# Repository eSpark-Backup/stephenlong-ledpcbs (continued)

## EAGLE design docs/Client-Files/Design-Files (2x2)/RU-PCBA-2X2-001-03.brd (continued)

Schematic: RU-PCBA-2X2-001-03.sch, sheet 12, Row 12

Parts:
C267, C268, C269, C270, C271, C272, C273, C274, C275, C276, C277, C278, C279, C280, C281, C282, C283, C284, C285, C286, C287, C288, C289, C290: C-EUC1206; C1206; MPN C_104
LD799, LD805, LD811, LD817, LD823, LD829, LD835, LD841, LD847, LD853, LD859, LD865: R; 5050LED; MPN R_5050
LD800, LD806, LD812, LD818, LD824, LD830, LD836, LD842, LD848, LD854, LD860, LD866: G; 5050LED; MPN G_5050
LD801, LD807, LD813, LD819, LD825, LD831, LD837, LD843, LD849, LD855, LD861, LD867: B; 5050LED; MPN B_5050
LD802, LD808, LD814, LD820, LD826, LD832, LD838, LD844, LD850, LD856, LD862, LD868: A; 5050LED; MPN A_5050
LD803, LD809, LD815, LD821, LD827, LD833, LD839, LD845, LD851, LD857, LD863, LD869: C; 5050LED; MPN C_5050
LD804, LD810, LD816, LD822, LD828, LD834, LD840, LD846, LD852, LD858, LD864, LD870: L; 5050LED; MPN L_5050
R1331, R1336, R1341, R1346, R1351, R1356, R1361, R1366, R1371, R1376, R1381, R1386, R1391, R1396, R1401, R1406, R1411, R1416, R1421, R1426, R1431, R1436, R1441, R1446: 2k; R1206; MPN R_VDD
R1332, R1333, R1337, R1338, R1342, R1343, R1347, R1348, R1352, R1353, R1357, R1358, R1362, R1363, R1367, R1368, R1372, R1373, R1377, R1378, R1382, R1383, R1387, R1388, R1392, R1393, R1397, R1398, R1402, R1403, R1407, R1408, R1412, R1413, R1417, R1418, R1422, R1423, R1427, R1428, R1432, R1433, R1437, R1438, R1442, R1443, R1447, R1448: 500; R0805; MPN R_500
R1334, R1339, R1344, R1349, R1354, R1359, R1364, R1369, R1374, R1379, R1384, R1389, R1394, R1399, R1404, R1409, R1414, R1419, R1424, R1429, R1434, R1439, R1444, R1449: 120; R0805; MPN R_120
R1335, R1340, R1345, R1350, R1355, R1360, R1365, R1370, R1375, R1380, R1385, R1390, R1395, R1400, R1405, R1410, R1415, R1420, R1425, R1430, R1435, R1440, R1445, R1450: 4.3K; R0805; MPN R_EXT
U265, U266, U267, U268, U269, U270, U271, U272, U273, U274, U275, U276, U277, U278, U279, U280, U281, U282, U283, U284, U285, U286, U287, U288: UCS7604; SOP100P600X175-10N; MPN UCS7604

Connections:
+24V: LD799.A, LD800.A, LD801.A, LD802.A, LD803.A, LD804.A, LD805.A, LD806.A, LD807.A, LD808.A, LD809.A, LD810.A, LD811.A, LD812.A, LD813.A, LD814.A, LD815.A, LD816.A, LD817.A, LD818.A, LD819.A, LD820.A, LD821.A, LD822.A, LD823.A, LD824.A, LD825.A, LD826.A, LD827.A, LD828.A, LD829.A, LD830.A, LD831.A, LD832.A, LD833.A, LD834.A, LD835.A, LD836.A, LD837.A, LD838.A, LD839.A, LD840.A, LD841.A, LD842.A, LD843.A, LD844.A, LD845.A, LD846.A, LD847.A, LD848.A, LD849.A, LD850.A, LD851.A, LD852.A, LD853.A, LD854.A, LD855.A, LD856.A, LD857.A, LD858.A, LD859.A, LD860.A, LD861.A, LD862.A, LD863.A, LD864.A, LD865.A, LD866.A, LD867.A, LD868.A, LD869.A, LD870.A, R1331.2, R1336.2, R1341.2, R1346.2, R1351.2, R1356.2, R1361.2, R1366.2, R1371.2, R1376.2, R1381.2, R1386.2, R1391.2, R1396.2, R1401.2, R1406.2, R1411.2, R1416.2, R1421.2, R1426.2, R1431.2, R1436.2, R1441.2, R1446.2; also elsewhere on the board
DOUT_U263: R1333.2; also elsewhere on the board
DOUT_U264: R1332.2, R1338.2; also elsewhere on the board
DOUT_U269: R1354.1, R1357.2, R1363.2
DOUT_U270: R1359.1, R1362.2, R1368.2
DOUT_U275: R1384.1, R1387.2, R1393.2
DOUT_U276: R1389.1, R1392.2, R1398.2
DOUT_U281: R1414.1, R1417.2, R1423.2
DOUT_U282: R1419.1, R1422.2, R1428.2
DOUT_U287: R1444.1, R1447.2; also elsewhere on the board
DOUT_U288: R1449.1; also elsewhere on the board
GND: C267.2, C268.2, C269.2, C270.2, C271.2, C272.2, C273.2, C274.2, C275.2, C276.2, C277.2, C278.2, C279.2, C280.2, C281.2, C282.2, C283.2, C284.2, C285.2, C286.2, C287.2, C288.2, C289.2, C290.2, R1335.1, R1340.1, R1345.1, R1350.1, R1355.1, R1360.1, R1365.1, R1370.1, R1375.1, R1380.1, R1385.1, R1390.1, R1395.1, R1400.1, R1405.1, R1410.1, R1415.1, R1420.1, R1425.1, R1430.1, R1435.1, R1440.1, R1445.1, R1450.1, U265.5 (GND), U266.5 (GND), U267.5 (GND), U268.5 (GND), U269.5 (GND), U270.5 (GND), U271.5 (GND), U272.5 (GND), U273.5 (GND), U274.5 (GND), U275.5 (GND), U276.5 (GND), U277.5 (GND), U278.5 (GND), U279.5 (GND), U280.5 (GND), U281.5 (GND), U282.5 (GND), U283.5 (GND), U284.5 (GND), U285.5 (GND), U286.5 (GND), U287.5 (GND), U288.5 (GND); also elsewhere on the board
unnamed: C267.1, R1331.1, U265.9 (VDD)
unnamed: LD799.K (C), U265.1 (R)
unnamed: LD800.K (C), U265.2 (G)
unnamed: LD801.K (C), U265.3 (B)
unnamed: R1332.1, U265.8 (DIN)
unnamed: R1333.1, U265.6 (FDIN)
unnamed: R1334.2, U265.10 (DOUT)
unnamed: R1335.2, U265.7 (REXT)
unnamed: LD802.K (C), U266.1 (R)
unnamed: LD803.K (C), U266.2 (G)
unnamed: LD804.K (C), U266.3 (B)
unnamed: C268.1, R1336.1, U266.9 (VDD)
unnamed: R1337.1, U266.8 (DIN)
unnamed: R1338.1, U266.6 (FDIN)
unnamed: R1339.2, U266.10 (DOUT)
unnamed: R1340.2, U266.7 (REXT)
unnamed: R1339.1, R1342.2, R1348.2
unnamed: C269.1, R1341.1, U267.9 (VDD)
unnamed: LD805.K (C), U267.1 (R)
unnamed: LD806.K (C), U267.2 (G)
unnamed: LD807.K (C), U267.3 (B)
unnamed: R1342.1, U267.8 (DIN)
unnamed: R1343.1, U267.6 (FDIN)
unnamed: R1344.2, U267.10 (DOUT)
unnamed: R1345.2, U267.7 (REXT)
unnamed: LD808.K (C), U268.1 (R)
unnamed: LD809.K (C), U268.2 (G)
unnamed: LD810.K (C), U268.3 (B)
unnamed: C270.1, R1346.1, U268.9 (VDD)
unnamed: R1347.1, U268.8 (DIN)
unnamed: R1344.1, R1347.2, R1353.2
unnamed: R1348.1, U268.6 (FDIN)
unnamed: R1334.1, R1337.2, R1343.2
unnamed: R1349.2, U268.10 (DOUT)
unnamed: R1350.2, U268.7 (REXT)
unnamed: R1349.1, R1352.2, R1358.2
unnamed: C271.1, R1351.1, U269.9 (VDD)
unnamed: LD811.K (C), U269.1 (R)
unnamed: LD812.K (C), U269.2 (G)
unnamed: LD813.K (C), U269.3 (B)
unnamed: R1352.1, U269.8 (DIN)
unnamed: R1353.1, U269.6 (FDIN)
unnamed: R1354.2, U269.10 (DOUT)
unnamed: R1355.2, U269.7 (REXT)
unnamed: LD814.K (C), U270.1 (R)
unnamed: LD815.K (C), U270.2 (G)
unnamed: LD816.K (C), U270.3 (B)
unnamed: C272.1, R1356.1, U270.9 (VDD)
unnamed: R1357.1, U270.8 (DIN)
unnamed: R1358.1, U270.6 (FDIN)
unnamed: R1359.2, U270.10 (DOUT)
unnamed: R1360.2, U270.7 (REXT)
unnamed: C273.1, R1361.1, U271.9 (VDD)
unnamed: LD817.K (C), U271.1 (R)
unnamed: LD818.K (C), U271.2 (G)
unnamed: LD819.K (C), U271.3 (B)
unnamed: R1362.1, U271.8 (DIN)
unnamed: R1363.1, U271.6 (FDIN)
unnamed: R1364.2, U271.10 (DOUT)
unnamed: R1365.2, U271.7 (REXT)
unnamed: LD820.K (C), U272.1 (R)
unnamed: LD821.K (C), U272.2 (G)
unnamed: LD822.K (C), U272.3 (B)
unnamed: C274.1, R1366.1, U272.9 (VDD)
unnamed: R1367.1, U272.8 (DIN)
unnamed: R1364.1, R1367.2, R1373.2
unnamed: R1368.1, U272.6 (FDIN)
unnamed: R1369.2, U272.10 (DOUT)
unnamed: R1370.2, U272.7 (REXT)
unnamed: R1369.1, R1372.2, R1378.2
unnamed: C275.1, R1371.1, U273.9 (VDD)
unnamed: LD823.K (C), U273.1 (R)
unnamed: LD824.K (C), U273.2 (G)
unnamed: LD825.K (C), U273.3 (B)
unnamed: R1372.1, U273.8 (DIN)
unnamed: R1373.1, U273.6 (FDIN)
unnamed: R1374.2, U273.10 (DOUT)
unnamed: R1375.2, U273.7 (REXT)
unnamed: LD826.K (C), U274.1 (R)
unnamed: LD827.K (C), U274.2 (G)
unnamed: LD828.K (C), U274.3 (B)
unnamed: C276.1, R1376.1, U274.9 (VDD)
unnamed: R1377.1, U274.8 (DIN)
unnamed: R1374.1, R1377.2, R1383.2
unnamed: R1378.1, U274.6 (FDIN)
unnamed: R1379.2, U274.10 (DOUT)
unnamed: R1380.2, U274.7 (REXT)
unnamed: R1379.1, R1382.2, R1388.2
unnamed: C277.1, R1381.1, U275.9 (VDD)
unnamed: LD829.K (C), U275.1 (R)
unnamed: LD830.K (C), U275.2 (G)
unnamed: LD831.K (C), U275.3 (B)
unnamed: R1382.1, U275.8 (DIN)
unnamed: R1383.1, U275.6 (FDIN)
unnamed: R1384.2, U275.10 (DOUT)
unnamed: R1385.2, U275.7 (REXT)
unnamed: LD832.K (C), U276.1 (R)
unnamed: LD833.K (C), U276.2 (G)
unnamed: LD834.K (C), U276.3 (B)
unnamed: C278.1, R1386.1, U276.9 (VDD)
unnamed: R1387.1, U276.8 (DIN)
unnamed: R1388.1, U276.6 (FDIN)
unnamed: R1389.2, U276.10 (DOUT)
unnamed: R1390.2, U276.7 (REXT)
unnamed: C279.1, R1391.1, U277.9 (VDD)
unnamed: LD835.K (C), U277.1 (R)
unnamed: LD836.K (C), U277.2 (G)
unnamed: LD837.K (C), U277.3 (B)
unnamed: R1392.1, U277.8 (DIN)
unnamed: R1393.1, U277.6 (FDIN)
unnamed: R1394.2, U277.10 (DOUT)
unnamed: R1395.2, U277.7 (REXT)
unnamed: LD838.K (C), U278.1 (R)
unnamed: LD839.K (C), U278.2 (G)
unnamed: LD840.K (C), U278.3 (B)
unnamed: C280.1, R1396.1, U278.9 (VDD)
unnamed: R1397.1, U278.8 (DIN)
unnamed: R1394.1, R1397.2, R1403.2
unnamed: R1398.1, U278.6 (FDIN)
unnamed: R1399.2, U278.10 (DOUT)
unnamed: R1400.2, U278.7 (REXT)
unnamed: C281.1, R1401.1, U279.9 (VDD)
unnamed: LD841.K (C), U279.1 (R)
unnamed: LD842.K (C), U279.2 (G)
unnamed: LD843.K (C), U279.3 (B)
unnamed: R1402.1, U279.8 (DIN)
unnamed: R1403.1, U279.6 (FDIN)
unnamed: R1404.2, U279.10 (DOUT)
unnamed: R1405.2, U279.7 (REXT)
unnamed: LD844.K (C), U280.1 (R)
unnamed: LD845.K (C), U280.2 (G)
unnamed: LD846.K (C), U280.3 (B)
unnamed: C282.1, R1406.1, U280.9 (VDD)
unnamed: R1407.1, U280.8 (DIN)
unnamed: R1404.1, R1407.2, R1413.2
unnamed: R1408.1, U280.6 (FDIN)
unnamed: R1399.1, R1402.2, R1408.2
unnamed: R1409.2, U280.10 (DOUT)
unnamed: R1410.2, U280.7 (REXT)
unnamed: R1409.1, R1412.2, R1418.2
unnamed: C283.1, R1411.1, U281.9 (VDD)
unnamed: LD847.K (C), U281.1 (R)
unnamed: LD848.K (C), U281.2 (G)
unnamed: LD849.K (C), U281.3 (B)
unnamed: R1412.1, U281.8 (DIN)
unnamed: R1413.1, U281.6 (FDIN)
unnamed: R1414.2, U281.10 (DOUT)
unnamed: R1415.2, U281.7 (REXT)
unnamed: LD850.K (C), U282.1 (R)
unnamed: LD851.K (C), U282.2 (G)
unnamed: LD852.K (C), U282.3 (B)
unnamed: C284.1, R1416.1, U282.9 (VDD)
unnamed: R1417.1, U282.8 (DIN)
unnamed: R1418.1, U282.6 (FDIN)
unnamed: R1419.2, U282.10 (DOUT)
unnamed: R1420.2, U282.7 (REXT)
unnamed: C285.1, R1421.1, U283.9 (VDD)
unnamed: LD853.K (C), U283.1 (R)
unnamed: LD854.K (C), U283.2 (G)
unnamed: LD855.K (C), U283.3 (B)
unnamed: R1422.1, U283.8 (DIN)
unnamed: R1423.1, U283.6 (FDIN)
unnamed: R1424.2, U283.10 (DOUT)
unnamed: R1425.2, U283.7 (REXT)
unnamed: LD856.K (C), U284.1 (R)
unnamed: LD857.K (C), U284.2 (G)
unnamed: LD858.K (C), U284.3 (B)
unnamed: C286.1, R1426.1, U284.9 (VDD)
unnamed: R1427.1, U284.8 (DIN)
unnamed: R1424.1, R1427.2, R1433.2
unnamed: R1428.1, U284.6 (FDIN)
unnamed: R1429.2, U284.10 (DOUT)
unnamed: R1430.2, U284.7 (REXT)
unnamed: R1429.1, R1432.2, R1438.2
unnamed: C287.1, R1431.1, U285.9 (VDD)
unnamed: LD859.K (C), U285.1 (R)
unnamed: LD860.K (C), U285.2 (G)
unnamed: LD861.K (C), U285.3 (B)
unnamed: R1432.1, U285.8 (DIN)
unnamed: R1433.1, U285.6 (FDIN)
unnamed: R1434.2, U285.10 (DOUT)
unnamed: R1435.2, U285.7 (REXT)
unnamed: LD862.K (C), U286.1 (R)
unnamed: LD863.K (C), U286.2 (G)
unnamed: LD864.K (C), U286.3 (B)
unnamed: C288.1, R1436.1, U286.9 (VDD)
unnamed: R1437.1, U286.8 (DIN)
unnamed: R1434.1, R1437.2, R1443.2
unnamed: R1438.1, U286.6 (FDIN)
unnamed: R1439.2, U286.10 (DOUT)
unnamed: R1440.2, U286.7 (REXT)
unnamed: R1439.1, R1442.2, R1448.2
unnamed: C289.1, R1441.1, U287.9 (VDD)
unnamed: LD865.K (C), U287.1 (R)
unnamed: LD866.K (C), U287.2 (G)
unnamed: LD867.K (C), U287.3 (B)
unnamed: R1442.1, U287.8 (DIN)
unnamed: R1443.1, U287.6 (FDIN)
unnamed: R1444.2, U287.10 (DOUT)
unnamed: R1445.2, U287.7 (REXT)
unnamed: LD868.K (C), U288.1 (R)
unnamed: LD869.K (C), U288.2 (G)
unnamed: LD870.K (C), U288.3 (B)
unnamed: C290.1, R1446.1, U288.9 (VDD)
unnamed: R1447.1, U288.8 (DIN)
unnamed: R1448.1, U288.6 (FDIN)
unnamed: R1449.2, U288.10 (DOUT)
unnamed: R1450.2, U288.7 (REXT)

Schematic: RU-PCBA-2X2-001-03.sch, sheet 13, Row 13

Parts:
C291, C292, C293, C294, C295, C296, C297, C298, C299, C300, C301, C302, C303, C304, C305, C306, C307, C308, C309, C310, C311, C312, C313, C314: C-EUC1206; C1206; MPN C_104
LD871, LD877, LD883, LD889, LD895, LD901, LD907, LD913, LD919, LD925, LD931, LD937: R; 5050LED; MPN R_5050
LD872, LD878, LD884, LD890, LD896, LD902, LD908, LD914, LD920, LD926, LD932, LD938: G; 5050LED; MPN G_5050
LD873, LD879, LD885, LD891, LD897, LD903, LD909, LD915, LD921, LD927, LD933, LD939: B; 5050LED; MPN B_5050
LD874, LD880, LD886, LD892, LD898, LD904, LD910, LD916, LD922, LD928, LD934, LD940: A; 5050LED; MPN A_5050
LD875, LD881, LD887, LD893, LD899, LD905, LD911, LD917, LD923, LD929, LD935, LD941: C; 5050LED; MPN C_5050
LD876, LD882, LD888, LD894, LD900, LD906, LD912, LD918, LD924, LD930, LD936, LD942: L; 5050LED; MPN L_5050
R1451, R1456, R1461, R1466, R1471, R1476, R1481, R1486, R1491, R1496, R1501, R1506, R1511, R1516, R1521, R1526, R1531, R1536, R1541, R1546, R1551, R1556, R1561, R1566: 2k; R1206; MPN R_VDD
R1452, R1453, R1457, R1458, R1462, R1463, R1467, R1468, R1472, R1473, R1477, R1478, R1482, R1483, R1487, R1488, R1492, R1493, R1497, R1498, R1502, R1503, R1507, R1508, R1512, R1513, R1517, R1518, R1522, R1523, R1527, R1528, R1532, R1533, R1537, R1538, R1542, R1543, R1547, R1548, R1552, R1553, R1557, R1558, R1562, R1563, R1567, R1568: 500; R0805; MPN R_500
R1454, R1459, R1464, R1469, R1474, R1479, R1484, R1489, R1494, R1499, R1504, R1509, R1514, R1519, R1524, R1529, R1534, R1539, R1544, R1549, R1554, R1559, R1564, R1569: 120; R0805; MPN R_120
R1455, R1460, R1465, R1470, R1475, R1480, R1485, R1490, R1495, R1500, R1505, R1510, R1515, R1520, R1525, R1530, R1535, R1540, R1545, R1550, R1555, R1560, R1565, R1570: 4.3K; R0805; MPN R_EXT
U289, U290, U291, U292, U293, U294, U295, U296, U297, U298, U299, U300, U301, U302, U303, U304, U305, U306, U307, U308, U309, U310, U311, U312: UCS7604; SOP100P600X175-10N; MPN UCS7604

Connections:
+24V: LD871.A, LD872.A, LD873.A, LD874.A, LD875.A, LD876.A, LD877.A, LD878.A, LD879.A, LD880.A, LD881.A, LD882.A, LD883.A, LD884.A, LD885.A, LD886.A, LD887.A, LD888.A, LD889.A, LD890.A, LD891.A, LD892.A, LD893.A, LD894.A, LD895.A, LD896.A, LD897.A, LD898.A, LD899.A, LD900.A, LD901.A, LD902.A, LD903.A, LD904.A, LD905.A, LD906.A, LD907.A, LD908.A, LD909.A, LD910.A, LD911.A, LD912.A, LD913.A, LD914.A, LD915.A, LD916.A, LD917.A, LD918.A, LD919.A, LD920.A, LD921.A, LD922.A, LD923.A, LD924.A, LD925.A, LD926.A, LD927.A, LD928.A, LD929.A, LD930.A, LD931.A, LD932.A, LD933.A, LD934.A, LD935.A, LD936.A, LD937.A, LD938.A, LD939.A, LD940.A, LD941.A, LD942.A, R1451.2, R1456.2, R1461.2, R1466.2, R1471.2, R1476.2, R1481.2, R1486.2, R1491.2, R1496.2, R1501.2, R1506.2, R1511.2, R1516.2, R1521.2, R1526.2, R1531.2, R1536.2, R1541.2, R1546.2, R1551.2, R1556.2, R1561.2, R1566.2; also elsewhere on the board
DOUT_U287: R1453.2; also elsewhere on the board
DOUT_U288: R1452.2, R1458.2; also elsewhere on the board
DOUT_U293: R1474.1, R1477.2, R1483.2
DOUT_U294: R1479.1, R1482.2, R1488.2
DOUT_U299: R1504.1, R1507.2, R1513.2
DOUT_U300: R1509.1, R1512.2, R1518.2
DOUT_U305: R1534.1, R1537.2, R1543.2
DOUT_U306: R1539.1, R1542.2, R1548.2
DOUT_U311: R1564.1, R1567.2; also elsewhere on the board
DOUT_U312: R1569.1; also elsewhere on the board
GND: C291.2, C292.2, C293.2, C294.2, C295.2, C296.2, C297.2, C298.2, C299.2, C300.2, C301.2, C302.2, C303.2, C304.2, C305.2, C306.2, C307.2, C308.2, C309.2, C310.2, C311.2, C312.2, C313.2, C314.2, R1455.1, R1460.1, R1465.1, R1470.1, R1475.1, R1480.1, R1485.1, R1490.1, R1495.1, R1500.1, R1505.1, R1510.1, R1515.1, R1520.1, R1525.1, R1530.1, R1535.1, R1540.1, R1545.1, R1550.1, R1555.1, R1560.1, R1565.1, R1570.1, U289.5 (GND), U290.5 (GND), U291.5 (GND), U292.5 (GND), U293.5 (GND), U294.5 (GND), U295.5 (GND), U296.5 (GND), U297.5 (GND), U298.5 (GND), U299.5 (GND), U300.5 (GND), U301.5 (GND), U302.5 (GND), U303.5 (GND), U304.5 (GND), U305.5 (GND), U306.5 (GND), U307.5 (GND), U308.5 (GND), U309.5 (GND), U310.5 (GND), U311.5 (GND), U312.5 (GND); also elsewhere on the board
unnamed: C291.1, R1451.1, U289.9 (VDD)
unnamed: LD871.K (C), U289.1 (R)
unnamed: LD872.K (C), U289.2 (G)
unnamed: LD873.K (C), U289.3 (B)
unnamed: R1452.1, U289.8 (DIN)
unnamed: R1453.1, U289.6 (FDIN)
unnamed: R1454.2, U289.10 (DOUT)
unnamed: R1455.2, U289.7 (REXT)
unnamed: LD874.K (C), U290.1 (R)
unnamed: LD875.K (C), U290.2 (G)
unnamed: LD876.K (C), U290.3 (B)
unnamed: C292.1, R1456.1, U290.9 (VDD)
unnamed: R1457.1, U290.8 (DIN)
unnamed: R1454.1, R1457.2, R1463.2
unnamed: R1458.1, U290.6 (FDIN)
unnamed: R1459.2, U290.10 (DOUT)
unnamed: R1460.2, U290.7 (REXT)
unnamed: R1459.1, R1462.2, R1468.2
unnamed: C293.1, R1461.1, U291.9 (VDD)
unnamed: LD877.K (C), U291.1 (R)
unnamed: LD878.K (C), U291.2 (G)
unnamed: LD879.K (C), U291.3 (B)
unnamed: R1462.1, U291.8 (DIN)
unnamed: R1463.1, U291.6 (FDIN)
unnamed: R1464.2, U291.10 (DOUT)
unnamed: R1465.2, U291.7 (REXT)
unnamed: LD880.K (C), U292.1 (R)
unnamed: LD881.K (C), U292.2 (G)
unnamed: LD882.K (C), U292.3 (B)
unnamed: C294.1, R1466.1, U292.9 (VDD)
unnamed: R1467.1, U292.8 (DIN)
unnamed: R1464.1, R1467.2, R1473.2
unnamed: R1468.1, U292.6 (FDIN)
unnamed: R1469.2, U292.10 (DOUT)
unnamed: R1470.2, U292.7 (REXT)
unnamed: R1469.1, R1472.2, R1478.2
unnamed: C295.1, R1471.1, U293.9 (VDD)
unnamed: LD883.K (C), U293.1 (R)
unnamed: LD884.K (C), U293.2 (G)
unnamed: LD885.K (C), U293.3 (B)
unnamed: R1472.1, U293.8 (DIN)
unnamed: R1473.1, U293.6 (FDIN)
unnamed: R1474.2, U293.10 (DOUT)
unnamed: R1475.2, U293.7 (REXT)
unnamed: LD886.K (C), U294.1 (R)
unnamed: LD887.K (C), U294.2 (G)
unnamed: LD888.K (C), U294.3 (B)
unnamed: C296.1, R1476.1, U294.9 (VDD)
unnamed: R1477.1, U294.8 (DIN)
unnamed: R1478.1, U294.6 (FDIN)
unnamed: R1479.2, U294.10 (DOUT)
unnamed: R1480.2, U294.7 (REXT)
unnamed: C297.1, R1481.1, U295.9 (VDD)
unnamed: LD889.K (C), U295.1 (R)
unnamed: LD890.K (C), U295.2 (G)
unnamed: LD891.K (C), U295.3 (B)
unnamed: R1482.1, U295.8 (DIN)
unnamed: R1483.1, U295.6 (FDIN)
unnamed: R1484.2, U295.10 (DOUT)
unnamed: R1485.2, U295.7 (REXT)
unnamed: LD892.K (C), U296.1 (R)
unnamed: LD893.K (C), U296.2 (G)
unnamed: LD894.K (C), U296.3 (B)
unnamed: C298.1, R1486.1, U296.9 (VDD)
unnamed: R1487.1, U296.8 (DIN)
unnamed: R1484.1, R1487.2, R1493.2
unnamed: R1488.1, U296.6 (FDIN)
unnamed: R1489.2, U296.10 (DOUT)
unnamed: R1490.2, U296.7 (REXT)
unnamed: R1489.1, R1492.2, R1498.2
unnamed: C299.1, R1491.1, U297.9 (VDD)
unnamed: LD895.K (C), U297.1 (R)
unnamed: LD896.K (C), U297.2 (G)
unnamed: LD897.K (C), U297.3 (B)
unnamed: R1492.1, U297.8 (DIN)
unnamed: R1493.1, U297.6 (FDIN)
unnamed: R1494.2, U297.10 (DOUT)
unnamed: R1495.2, U297.7 (REXT)
unnamed: LD898.K (C), U298.1 (R)
unnamed: LD899.K (C), U298.2 (G)
unnamed: LD900.K (C), U298.3 (B)
unnamed: C300.1, R1496.1, U298.9 (VDD)
unnamed: R1497.1, U298.8 (DIN)
unnamed: R1494.1, R1497.2, R1503.2
unnamed: R1498.1, U298.6 (FDIN)
unnamed: R1499.2, U298.10 (DOUT)
unnamed: R1500.2, U298.7 (REXT)
unnamed: R1499.1, R1502.2, R1508.2
unnamed: C301.1, R1501.1, U299.9 (VDD)
unnamed: LD901.K (C), U299.1 (R)
unnamed: LD902.K (C), U299.2 (G)
unnamed: LD903.K (C), U299.3 (B)
unnamed: R1502.1, U299.8 (DIN)
unnamed: R1503.1, U299.6 (FDIN)
unnamed: R1504.2, U299.10 (DOUT)
unnamed: R1505.2, U299.7 (REXT)
unnamed: LD904.K (C), U300.1 (R)
unnamed: LD905.K (C), U300.2 (G)
unnamed: LD906.K (C), U300.3 (B)
unnamed: C302.1, R1506.1, U300.9 (VDD)
unnamed: R1507.1, U300.8 (DIN)
unnamed: R1508.1, U300.6 (FDIN)
unnamed: R1509.2, U300.10 (DOUT)
unnamed: R1510.2, U300.7 (REXT)
unnamed: C303.1, R1511.1, U301.9 (VDD)
unnamed: LD907.K (C), U301.1 (R)
unnamed: LD908.K (C), U301.2 (G)
unnamed: LD909.K (C), U301.3 (B)
unnamed: R1512.1, U301.8 (DIN)
unnamed: R1513.1, U301.6 (FDIN)
unnamed: R1514.2, U301.10 (DOUT)
unnamed: R1515.2, U301.7 (REXT)
unnamed: LD910.K (C), U302.1 (R)
unnamed: LD911.K (C), U302.2 (G)
unnamed: LD912.K (C), U302.3 (B)
unnamed: C304.1, R1516.1, U302.9 (VDD)
unnamed: R1517.1, U302.8 (DIN)
unnamed: R1514.1, R1517.2, R1523.2
unnamed: R1518.1, U302.6 (FDIN)
unnamed: R1519.2, U302.10 (DOUT)
unnamed: R1520.2, U302.7 (REXT)
unnamed: R1519.1, R1522.2, R1528.2
unnamed: C305.1, R1521.1, U303.9 (VDD)
unnamed: LD913.K (C), U303.1 (R)
unnamed: LD914.K (C), U303.2 (G)
unnamed: LD915.K (C), U303.3 (B)
unnamed: R1522.1, U303.8 (DIN)
unnamed: R1523.1, U303.6 (FDIN)
unnamed: R1524.2, U303.10 (DOUT)
unnamed: R1525.2, U303.7 (REXT)
unnamed: LD916.K (C), U304.1 (R)
unnamed: LD917.K (C), U304.2 (G)
unnamed: LD918.K (C), U304.3 (B)
unnamed: C306.1, R1526.1, U304.9 (VDD)
unnamed: R1527.1, U304.8 (DIN)
unnamed: R1524.1, R1527.2, R1533.2
unnamed: R1528.1, U304.6 (FDIN)
unnamed: R1529.2, U304.10 (DOUT)
unnamed: R1530.2, U304.7 (REXT)
unnamed: R1529.1, R1532.2, R1538.2
unnamed: C307.1, R1531.1, U305.9 (VDD)
unnamed: LD919.K (C), U305.1 (R)
unnamed: LD920.K (C), U305.2 (G)
unnamed: LD921.K (C), U305.3 (B)
unnamed: R1532.1, U305.8 (DIN)
unnamed: R1533.1, U305.6 (FDIN)
unnamed: R1534.2, U305.10 (DOUT)
unnamed: R1535.2, U305.7 (REXT)
unnamed: LD922.K (C), U306.1 (R)
unnamed: LD923.K (C), U306.2 (G)
unnamed: LD924.K (C), U306.3 (B)
unnamed: C308.1, R1536.1, U306.9 (VDD)
unnamed: R1537.1, U306.8 (DIN)
unnamed: R1538.1, U306.6 (FDIN)
unnamed: R1539.2, U306.10 (DOUT)
unnamed: R1540.2, U306.7 (REXT)
unnamed: C309.1, R1541.1, U307.9 (VDD)
unnamed: LD925.K (C), U307.1 (R)
unnamed: LD926.K (C), U307.2 (G)
unnamed: LD927.K (C), U307.3 (B)
unnamed: R1542.1, U307.8 (DIN)
unnamed: R1543.1, U307.6 (FDIN)
unnamed: R1544.2, U307.10 (DOUT)
unnamed: R1545.2, U307.7 (REXT)
unnamed: LD928.K (C), U308.1 (R)
unnamed: LD929.K (C), U308.2 (G)
unnamed: LD930.K (C), U308.3 (B)
unnamed: C310.1, R1546.1, U308.9 (VDD)
unnamed: R1547.1, U308.8 (DIN)
unnamed: R1544.1, R1547.2, R1553.2
unnamed: R1548.1, U308.6 (FDIN)
unnamed: R1549.2, U308.10 (DOUT)
unnamed: R1550.2, U308.7 (REXT)
unnamed: R1549.1, R1552.2, R1558.2
unnamed: C311.1, R1551.1, U309.9 (VDD)
unnamed: LD931.K (C), U309.1 (R)
unnamed: LD932.K (C), U309.2 (G)
unnamed: LD933.K (C), U309.3 (B)
unnamed: R1552.1, U309.8 (DIN)
unnamed: R1553.1, U309.6 (FDIN)
unnamed: R1554.2, U309.10 (DOUT)
unnamed: R1555.2, U309.7 (REXT)
unnamed: LD934.K (C), U310.1 (R)
unnamed: LD935.K (C), U310.2 (G)
unnamed: LD936.K (C), U310.3 (B)
unnamed: C312.1, R1556.1, U310.9 (VDD)
unnamed: R1557.1, U310.8 (DIN)
unnamed: R1554.1, R1557.2, R1563.2
unnamed: R1558.1, U310.6 (FDIN)
unnamed: R1559.2, U310.10 (DOUT)
unnamed: R1560.2, U310.7 (REXT)
unnamed: R1559.1, R1562.2, R1568.2
unnamed: C313.1, R1561.1, U311.9 (VDD)
unnamed: LD937.K (C), U311.1 (R)
unnamed: LD938.K (C), U311.2 (G)
unnamed: LD939.K (C), U311.3 (B)
unnamed: R1562.1, U311.8 (DIN)
unnamed: R1563.1, U311.6 (FDIN)
unnamed: R1564.2, U311.10 (DOUT)
unnamed: R1565.2, U311.7 (REXT)
unnamed: LD940.K (C), U312.1 (R)
unnamed: LD941.K (C), U312.2 (G)
unnamed: LD942.K (C), U312.3 (B)
unnamed: C314.1, R1566.1, U312.9 (VDD)
unnamed: R1567.1, U312.8 (DIN)
unnamed: R1568.1, U312.6 (FDIN)
unnamed: R1569.2, U312.10 (DOUT)
unnamed: R1570.2, U312.7 (REXT)

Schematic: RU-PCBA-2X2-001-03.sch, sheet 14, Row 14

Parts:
C315, C316, C317, C318, C319, C320, C321, C322, C323, C324, C325, C326, C327, C328, C329, C330, C331, C332, C333, C334, C335, C336, C337, C338: C-EUC1206; C1206; MPN C_104
LD943, LD949, LD955, LD961, LD967, LD973, LD979, LD985, LD991, LD997, LD1003, LD1009: R; 5050LED; MPN R_5050
LD944, LD950, LD956, LD962, LD968, LD974, LD980, LD986, LD992, LD998, LD1004, LD1010: G; 5050LED; MPN G_5050
LD945, LD951, LD957, LD963, LD969, LD975, LD981, LD987, LD993, LD999, LD1005, LD1011: B; 5050LED; MPN B_5050
LD946, LD952, LD958, LD964, LD970, LD976, LD982, LD988, LD994, LD1000, LD1006, LD1012: A; 5050LED; MPN A_5050
LD947, LD953, LD959, LD965, LD971, LD977, LD983, LD989, LD995, LD1001, LD1007, LD1013: C; 5050LED; MPN C_5050
LD948, LD954, LD960, LD966, LD972, LD978, LD984, LD990, LD996, LD1002, LD1008, LD1014: L; 5050LED; MPN L_5050
R1571, R1576, R1581, R1586, R1591, R1596, R1601, R1606, R1611, R1616, R1621, R1626, R1631, R1636, R1641, R1646, R1651, R1656, R1661, R1666, R1671, R1676, R1681, R1686: 2k; R1206; MPN R_VDD
R1572, R1573, R1577, R1578, R1582, R1583, R1587, R1588, R1592, R1593, R1597, R1598, R1602, R1603, R1607, R1608, R1612, R1613, R1617, R1618, R1622, R1623, R1627, R1628, R1632, R1633, R1637, R1638, R1642, R1643, R1647, R1648, R1652, R1653, R1657, R1658, R1662, R1663, R1667, R1668, R1672, R1673, R1677, R1678, R1682, R1683, R1687, R1688: 500; R0805; MPN R_500
R1574, R1579, R1584, R1589, R1594, R1599, R1604, R1609, R1614, R1619, R1624, R1629, R1634, R1639, R1644, R1649, R1654, R1659, R1664, R1669, R1674, R1679, R1684, R1689: 120; R0805; MPN R_120
R1575, R1580, R1585, R1590, R1595, R1600, R1605, R1610, R1615, R1620, R1625, R1630, R1635, R1640, R1645, R1650, R1655, R1660, R1665, R1670, R1675, R1680, R1685, R1690: 4.3K; R0805; MPN R_EXT
U313, U314, U315, U316, U317, U318, U319, U320, U321, U322, U323, U324, U325, U326, U327, U328, U329, U330, U331, U332, U333, U334, U335, U336: UCS7604; SOP100P600X175-10N; MPN UCS7604

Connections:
+24V: LD943.A, LD944.A, LD945.A, LD946.A, LD947.A, LD948.A, LD949.A, LD950.A, LD951.A, LD952.A, LD953.A, LD954.A, LD955.A, LD956.A, LD957.A, LD958.A, LD959.A, LD960.A, LD961.A, LD962.A, LD963.A, LD964.A, LD965.A, LD966.A, LD967.A, LD968.A, LD969.A, LD970.A, LD971.A, LD972.A, LD973.A, LD974.A, LD975.A, LD976.A, LD977.A, LD978.A, LD979.A, LD980.A, LD981.A, LD982.A, LD983.A, LD984.A, LD985.A, LD986.A, LD987.A, LD988.A, LD989.A, LD990.A, LD991.A, LD992.A, LD993.A, LD994.A, LD995.A, LD996.A, LD997.A, LD998.A, LD999.A, LD1000.A, LD1001.A, LD1002.A, LD1003.A, LD1004.A, LD1005.A, LD1006.A, LD1007.A, LD1008.A, LD1009.A, LD1010.A, LD1011.A, LD1012.A, LD1013.A, LD1014.A, R1571.2, R1576.2, R1581.2, R1586.2, R1591.2, R1596.2, R1601.2, R1606.2, R1611.2, R1616.2, R1621.2, R1626.2, R1631.2, R1636.2, R1641.2, R1646.2, R1651.2, R1656.2, R1661.2, R1666.2, R1671.2, R1676.2, R1681.2, R1686.2; also elsewhere on the board
DOUT_TRM1_UNI2: R1689.1
DOUT_TRM2_UNI2: R1684.1, R1687.2
DOUT_U311: R1573.2; also elsewhere on the board
DOUT_U312: R1572.2, R1578.2; also elsewhere on the board
DOUT_U317: R1594.1, R1597.2, R1603.2
DOUT_U318: R1599.1, R1602.2, R1608.2
DOUT_U323: R1624.1, R1627.2, R1633.2
DOUT_U324: R1629.1, R1632.2, R1638.2
DOUT_U329: R1654.1, R1657.2, R1663.2
DOUT_U330: R1659.1, R1662.2, R1668.2
GND: C315.2, C316.2, C317.2, C318.2, C319.2, C320.2, C321.2, C322.2, C323.2, C324.2, C325.2, C326.2, C327.2, C328.2, C329.2, C330.2, C331.2, C332.2, C333.2, C334.2, C335.2, C336.2, C337.2, C338.2, R1575.1, R1580.1, R1585.1, R1590.1, R1595.1, R1600.1, R1605.1, R1610.1, R1615.1, R1620.1, R1625.1, R1630.1, R1635.1, R1640.1, R1645.1, R1650.1, R1655.1, R1660.1, R1665.1, R1670.1, R1675.1, R1680.1, R1685.1, R1690.1, U313.5 (GND), U314.5 (GND), U315.5 (GND), U316.5 (GND), U317.5 (GND), U318.5 (GND), U319.5 (GND), U320.5 (GND), U321.5 (GND), U322.5 (GND), U323.5 (GND), U324.5 (GND), U325.5 (GND), U326.5 (GND), U327.5 (GND), U328.5 (GND), U329.5 (GND), U330.5 (GND), U331.5 (GND), U332.5 (GND), U333.5 (GND), U334.5 (GND), U335.5 (GND), U336.5 (GND); also elsewhere on the board
unnamed: C315.1, R1571.1, U313.9 (VDD)
unnamed: LD943.K (C), U313.1 (R)
unnamed: LD944.K (C), U313.2 (G)
unnamed: LD945.K (C), U313.3 (B)
unnamed: R1572.1, U313.8 (DIN)
unnamed: R1573.1, U313.6 (FDIN)
unnamed: R1574.2, U313.10 (DOUT)
unnamed: R1575.2, U313.7 (REXT)
unnamed: LD946.K (C), U314.1 (R)
unnamed: LD947.K (C), U314.2 (G)
unnamed: LD948.K (C), U314.3 (B)
unnamed: C316.1, R1576.1, U314.9 (VDD)
unnamed: R1577.1, U314.8 (DIN)
unnamed: R1574.1, R1577.2, R1583.2
unnamed: R1578.1, U314.6 (FDIN)
unnamed: R1579.2, U314.10 (DOUT)
unnamed: R1580.2, U314.7 (REXT)
unnamed: C317.1, R1581.1, U315.9 (VDD)
unnamed: LD949.K (C), U315.1 (R)
unnamed: LD950.K (C), U315.2 (G)
unnamed: LD951.K (C), U315.3 (B)
unnamed: R1582.1, U315.8 (DIN)
unnamed: R1583.1, U315.6 (FDIN)
unnamed: R1584.2, U315.10 (DOUT)
unnamed: R1585.2, U315.7 (REXT)
unnamed: LD952.K (C), U316.1 (R)
unnamed: LD953.K (C), U316.2 (G)
unnamed: LD954.K (C), U316.3 (B)
unnamed: C318.1, R1586.1, U316.9 (VDD)
unnamed: R1587.1, U316.8 (DIN)
unnamed: R1584.1, R1587.2, R1593.2
unnamed: R1588.1, U316.6 (FDIN)
unnamed: R1579.1, R1582.2, R1588.2
unnamed: R1589.2, U316.10 (DOUT)
unnamed: R1590.2, U316.7 (REXT)
unnamed: R1589.1, R1592.2, R1598.2
unnamed: C319.1, R1591.1, U317.9 (VDD)
unnamed: LD955.K (C), U317.1 (R)
unnamed: LD956.K (C), U317.2 (G)
unnamed: LD957.K (C), U317.3 (B)
unnamed: R1592.1, U317.8 (DIN)
unnamed: R1593.1, U317.6 (FDIN)
unnamed: R1594.2, U317.10 (DOUT)
unnamed: R1595.2, U317.7 (REXT)
unnamed: LD958.K (C), U318.1 (R)
unnamed: LD959.K (C), U318.2 (G)
unnamed: LD960.K (C), U318.3 (B)
unnamed: C320.1, R1596.1, U318.9 (VDD)
unnamed: R1597.1, U318.8 (DIN)
unnamed: R1598.1, U318.6 (FDIN)
unnamed: R1599.2, U318.10 (DOUT)
unnamed: R1600.2, U318.7 (REXT)
unnamed: C321.1, R1601.1, U319.9 (VDD)
unnamed: LD961.K (C), U319.1 (R)
unnamed: LD962.K (C), U319.2 (G)
unnamed: LD963.K (C), U319.3 (B)
unnamed: R1602.1, U319.8 (DIN)
unnamed: R1603.1, U319.6 (FDIN)
unnamed: R1604.2, U319.10 (DOUT)
unnamed: R1605.2, U319.7 (REXT)
unnamed: LD964.K (C), U320.1 (R)
unnamed: LD965.K (C), U320.2 (G)
unnamed: LD966.K (C), U320.3 (B)
unnamed: C322.1, R1606.1, U320.9 (VDD)
unnamed: R1607.1, U320.8 (DIN)
unnamed: R1604.1, R1607.2, R1613.2
unnamed: R1608.1, U320.6 (FDIN)
unnamed: R1609.2, U320.10 (DOUT)
unnamed: R1610.2, U320.7 (REXT)
unnamed: R1609.1, R1612.2, R1618.2
unnamed: C323.1, R1611.1, U321.9 (VDD)
unnamed: LD967.K (C), U321.1 (R)
unnamed: LD968.K (C), U321.2 (G)
unnamed: LD969.K (C), U321.3 (B)
unnamed: R1612.1, U321.8 (DIN)
unnamed: R1613.1, U321.6 (FDIN)
unnamed: R1614.2, U321.10 (DOUT)
unnamed: R1615.2, U321.7 (REXT)
unnamed: LD970.K (C), U322.1 (R)
unnamed: LD971.K (C), U322.2 (G)
unnamed: LD972.K (C), U322.3 (B)
unnamed: C324.1, R1616.1, U322.9 (VDD)
unnamed: R1617.1, U322.8 (DIN)
unnamed: R1614.1, R1617.2, R1623.2
unnamed: R1618.1, U322.6 (FDIN)
unnamed: R1619.2, U322.10 (DOUT)
unnamed: R1620.2, U322.7 (REXT)
unnamed: R1619.1, R1622.2, R1628.2
unnamed: C325.1, R1621.1, U323.9 (VDD)
unnamed: LD973.K (C), U323.1 (R)
unnamed: LD974.K (C), U323.2 (G)
unnamed: LD975.K (C), U323.3 (B)
unnamed: R1622.1, U323.8 (DIN)
unnamed: R1623.1, U323.6 (FDIN)
unnamed: R1624.2, U323.10 (DOUT)
unnamed: R1625.2, U323.7 (REXT)
unnamed: LD976.K (C), U324.1 (R)
unnamed: LD977.K (C), U324.2 (G)
unnamed: LD978.K (C), U324.3 (B)
unnamed: C326.1, R1626.1, U324.9 (VDD)
unnamed: R1627.1, U324.8 (DIN)
unnamed: R1628.1, U324.6 (FDIN)
unnamed: R1629.2, U324.10 (DOUT)
unnamed: R1630.2, U324.7 (REXT)
unnamed: C327.1, R1631.1, U325.9 (VDD)
unnamed: LD979.K (C), U325.1 (R)
unnamed: LD980.K (C), U325.2 (G)
unnamed: LD981.K (C), U325.3 (B)
unnamed: R1632.1, U325.8 (DIN)
unnamed: R1633.1, U325.6 (FDIN)
unnamed: R1634.2, U325.10 (DOUT)
unnamed: R1635.2, U325.7 (REXT)
unnamed: LD982.K (C), U326.1 (R)
unnamed: LD983.K (C), U326.2 (G)
unnamed: LD984.K (C), U326.3 (B)
unnamed: C328.1, R1636.1, U326.9 (VDD)
unnamed: R1637.1, U326.8 (DIN)
unnamed: R1634.1, R1637.2, R1643.2
unnamed: R1638.1, U326.6 (FDIN)
unnamed: R1639.2, U326.10 (DOUT)
unnamed: R1640.2, U326.7 (REXT)
unnamed: R1639.1, R1642.2, R1648.2
unnamed: C329.1, R1641.1, U327.9 (VDD)
unnamed: LD985.K (C), U327.1 (R)
unnamed: LD986.K (C), U327.2 (G)
unnamed: LD987.K (C), U327.3 (B)
unnamed: R1642.1, U327.8 (DIN)
unnamed: R1643.1, U327.6 (FDIN)
unnamed: R1644.2, U327.10 (DOUT)
unnamed: R1645.2, U327.7 (REXT)
unnamed: LD988.K (C), U328.1 (R)
unnamed: LD989.K (C), U328.2 (G)
unnamed: LD990.K (C), U328.3 (B)
unnamed: C330.1, R1646.1, U328.9 (VDD)
unnamed: R1647.1, U328.8 (DIN)
unnamed: R1648.1, U328.6 (FDIN)
unnamed: R1649.2, U328.10 (DOUT)
unnamed: R1650.2, U328.7 (REXT)
unnamed: R1649.1, R1652.2, R1658.2
unnamed: C331.1, R1651.1, U329.9 (VDD)
unnamed: LD991.K (C), U329.1 (R)
unnamed: LD992.K (C), U329.2 (G)
unnamed: LD993.K (C), U329.3 (B)
unnamed: R1652.1, U329.8 (DIN)
unnamed: R1653.1, U329.6 (FDIN)
unnamed: R1654.2, U329.10 (DOUT)
unnamed: R1655.2, U329.7 (REXT)
unnamed: LD994.K (C), U330.1 (R)
unnamed: LD995.K (C), U330.2 (G)
unnamed: LD996.K (C), U330.3 (B)
unnamed: C332.1, R1656.1, U330.9 (VDD)
unnamed: R1657.1, U330.8 (DIN)
unnamed: R1658.1, U330.6 (FDIN)
unnamed: R1644.1, R1647.2, R1653.2
unnamed: R1659.2, U330.10 (DOUT)
unnamed: R1660.2, U330.7 (REXT)
unnamed: C333.1, R1661.1, U331.9 (VDD)
unnamed: LD997.K (C), U331.1 (R)
unnamed: LD998.K (C), U331.2 (G)
unnamed: LD999.K (C), U331.3 (B)
unnamed: R1662.1, U331.8 (DIN)
unnamed: R1663.1, U331.6 (FDIN)
unnamed: R1664.2, U331.10 (DOUT)
unnamed: R1665.2, U331.7 (REXT)
unnamed: LD1000.K (C), U332.1 (R)
unnamed: LD1001.K (C), U332.2 (G)
unnamed: LD1002.K (C), U332.3 (B)
unnamed: C334.1, R1666.1, U332.9 (VDD)
unnamed: R1667.1, U332.8 (DIN)
unnamed: R1664.1, R1667.2, R1673.2
unnamed: R1668.1, U332.6 (FDIN)
unnamed: R1669.2, U332.10 (DOUT)
unnamed: R1670.2, U332.7 (REXT)
unnamed: R1669.1, R1672.2, R1678.2
unnamed: C335.1, R1671.1, U333.9 (VDD)
unnamed: LD1003.K (C), U333.1 (R)
unnamed: LD1004.K (C), U333.2 (G)
unnamed: LD1005.K (C), U333.3 (B)
unnamed: R1672.1, U333.8 (DIN)
unnamed: R1673.1, U333.6 (FDIN)
unnamed: R1674.2, U333.10 (DOUT)
unnamed: R1675.2, U333.7 (REXT)
unnamed: LD1006.K (C), U334.1 (R)
unnamed: LD1007.K (C), U334.2 (G)
unnamed: LD1008.K (C), U334.3 (B)
unnamed: C336.1, R1676.1, U334.9 (VDD)
unnamed: R1677.1, U334.8 (DIN)
unnamed: R1674.1, R1677.2, R1683.2
unnamed: R1678.1, U334.6 (FDIN)
unnamed: R1679.2, U334.10 (DOUT)
unnamed: R1680.2, U334.7 (REXT)
unnamed: R1679.1, R1682.2, R1688.2
unnamed: C337.1, R1681.1, U335.9 (VDD)
unnamed: LD1009.K (C), U335.1 (R)
unnamed: LD1010.K (C), U335.2 (G)
unnamed: LD1011.K (C), U335.3 (B)
unnamed: R1682.1, U335.8 (DIN)
unnamed: R1683.1, U335.6 (FDIN)
unnamed: R1684.2, U335.10 (DOUT)
unnamed: R1685.2, U335.7 (REXT)
unnamed: LD1012.K (C), U336.1 (R)
unnamed: LD1013.K (C), U336.2 (G)
unnamed: LD1014.K (C), U336.3 (B)
unnamed: C338.1, R1686.1, U336.9 (VDD)
unnamed: R1687.1, U336.8 (DIN)
unnamed: R1688.1, U336.6 (FDIN)
unnamed: R1689.2, U336.10 (DOUT)
unnamed: R1690.2, U336.7 (REXT)

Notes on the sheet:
End Universe 2

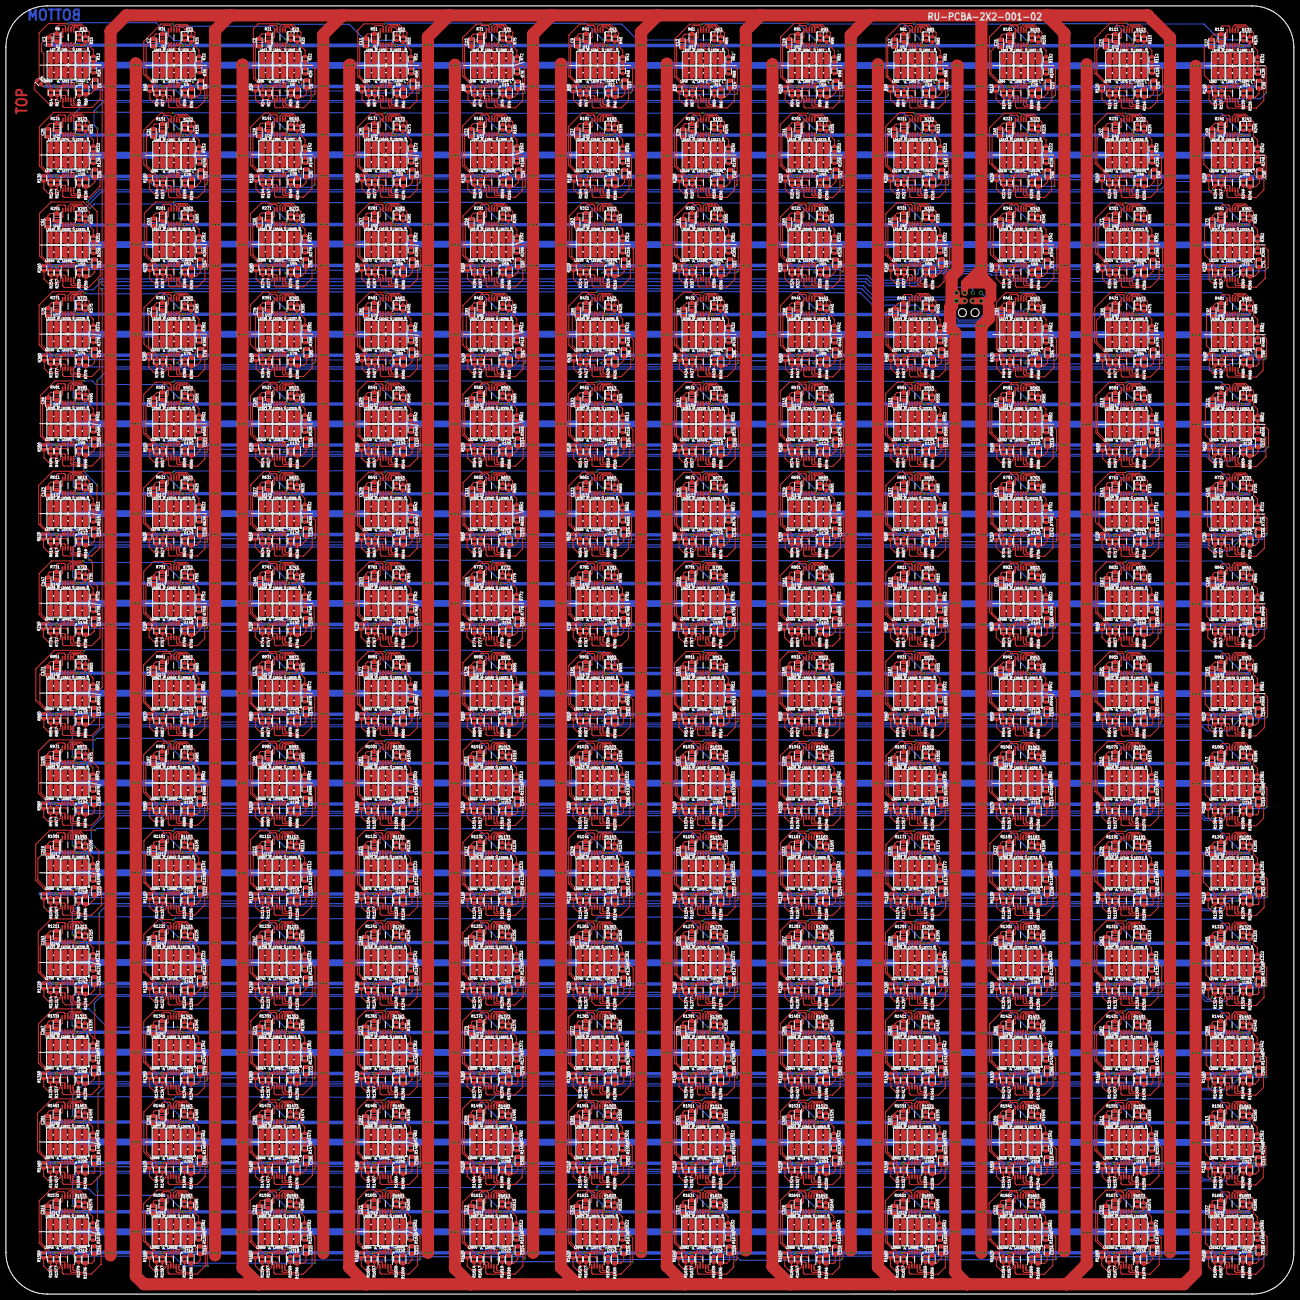
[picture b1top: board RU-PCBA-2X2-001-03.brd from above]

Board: 2 copper layers, 475.0 x 475.1 mm, 3361 parts (1 on the bottom side), 3026 nets.

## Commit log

2025-04-29 Add: 2x2 reference design
2025-04-29 Update PRD - v1.3 (both designs)
2025-04-29 Format: PRD - v1
2025-04-30 #1 Complete. PDF generated
2025-04-30 #1 PCB In Progress.
2025-04-30 #1 Client BOM added.
2025-04-30 #1 Routing in Progress
2025-04-30 #1 Selectable direct drive or IC drive shunt scheme through headers added. PDF updated
2025-05-01 #1 PCB Completed and Deliverables Generated
2025-05-02 Remove: Extra schematic PDFs
2025-05-02 Update PRD - v1
2025-05-02 #1 Company logo added and deliverables generated
2025-05-02 Remove: Extra schematic
